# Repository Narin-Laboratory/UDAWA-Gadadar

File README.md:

# UDAWA Gadadar - Universal Digital Agriculture Workflow Assistant

Welcome to the official firmware repository for UDAWA Gadadar, a key component of the UDAWA Smart System! This project is dedicated to empowering small-scale farmers with precision agriculture technology, making farming more efficient, sustainable, and fun.

## What is UDAWA?

UDAWA, which stands for **Universal Digital Agriculture Workflow Assistant**, is an open-source platform designed to bring the power of the Internet of Things (IoT) to agriculture. Our mission is to create a "peasant-centric" ecosystem of hardware and software tools that are affordable, easy to use, and adaptable to the needs of small farmers.

We believe that technology can help bridge the gap between traditional farming practices and modern, data-driven agriculture. By providing tools for monitoring, control, and automation, UDAWA helps farmers save time, reduce waste, and gain valuable insights into their operations.

## UDAWA Gadadar: The Smart Power Controller

UDAWA Gadadar is the muscle of the UDAWA ecosystem. It's a smart power controller that allows you to manage and automate various electrical appliances in your greenhouse or farm, such as:

- Pumps for irrigation and fertigation
- Fans and blowers for climate control
- Grow lights for supplemental lighting
- Misters and foggers for humidity control

### Key Features:

- **Remote Control:** Turn your farm equipment on and off from anywhere using your smartphone.
- **Automation:** Schedule tasks based on time, duration, or sensor data (e.g., turn on the fan when the temperature rises).
- **Energy Monitoring:** Keep track of your electricity consumption to optimize usage and reduce costs.
- **Modular Design:** UDAWA Gadadar comes with four independent channels, each with its own energy sensor.
- **Open Source:** The firmware is fully open-source, allowing you to customize and extend its functionality.

## Hardware

The UDAWA Gadadar hardware is designed to be robust, reliable, and easy to assemble. Here's a sneak peek at the device:

**Image Placeholder: UDAWA Gadadar Device**
``

## Software

The UDAWA Gadadar firmware is built on the PlatformIO ecosystem and runs on the popular ESP32 microcontroller. It's packed with features to ensure seamless integration with the UDAWA cloud platform and mobile app.

**Image Placeholder: UDAWA Mobile App Screenshot**
``

## Getting Started

Ready to build your own UDAWA Gadadar? Here's how to get started:

1. **Set up your environment:**
   ```bash
   ./setup_env.sh
   ```
2. **Build the firmware:**
   ```bash
   pio run -e Gadadar4Ch
   ```
3. **Upload the firmware to your ESP32.**
4. **Provision your device using the UDAWA mobile app.**

For more detailed instructions, please refer to our documentation (coming soon!).

## Contributing

UDAWA is a community-driven project, and we welcome contributions from everyone! Whether you're a farmer, an engineer, a developer, or a hobbyist, there are many ways you can get involved:

- **Report bugs and suggest features** by opening an issue.
- **Submit pull requests** with your own code, documentation, or design improvements.
- **Share your UDAWA projects** with the community.

## Our Dearest Contributors

This project would not be possible without the amazing contributions of the following individuals:

- I Wayan Aditya Suranata
- I Nyoman Kusuma Wardana
- Ngakan Kutha Krisnawijaya
- Gede Humaswara Prathama
- Dhimas Prayoga
- I Made Surya Adi Putra
- I Gusti Ngurah Darma Paramartha
- Adie Wahyudi Oktavia Gama
- I Putu Widia Prasetya
- I Nyoman Hary Kurniawan
- I Made Pande Darma Yuda
- I Kadek Arta Wiguna
- I Gusti Gede Dhipa Andaresta
- Hendri Gunawan
- Andhika Bintar Lorenzo Kristian Reinnamah
- I Gusti Nathan Agung Tanaka
- Muhammad Zafran Zulkifli
- You

## License

UDAWA Gadadar is licensed under the **GNU Affero General Public License v3.0**. This means you are free to use, modify, and distribute the software, but you must also make your modifications available under the same license. For more details, see the [LICENSE](LICENSE) file.

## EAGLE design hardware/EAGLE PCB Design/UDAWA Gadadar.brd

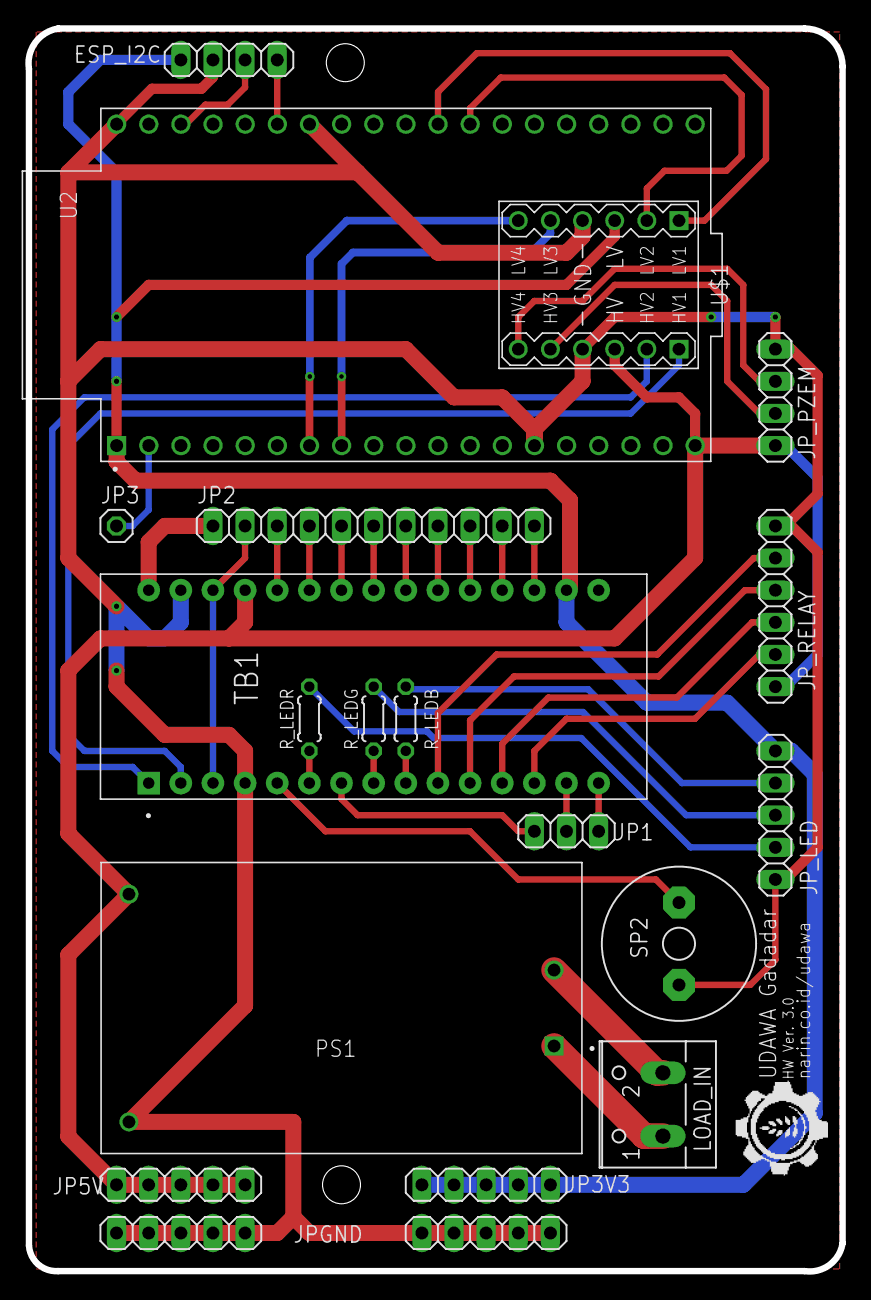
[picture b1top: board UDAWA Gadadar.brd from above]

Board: 2 copper layers, 64.3 x 98.2 mm, 20 parts (0 on the bottom side), 41 nets.

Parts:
ESP_I2C: 1X04
JP1: 1X03
JP2: 1X11
JP3: PINHD-1X1; 1X01
JP3V3, JP5V: 1X05
JPGND, JPGND1: 1X05
JP_LED: 1X05
JP_PZEM: 1X04
JP_RELAY: 1X06
LOAD_IN: W237-102
PS1: HLK-5M05; CONV_HLK-5M05
R_LEDB: 1K; 0204/5
R_LEDG: 1K; 0204/5
R_LEDR: 1K; 0204/5
SP2: AL60P
TB1: ARDUINO_NANO; SHIELD_ARDUINO_NANO
U2: ESP32-DEVKITC-32U; MODULE_ESP32-DEVKITC-32U
U$1: LEVEL-SHIFTER-4CH

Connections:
3V3: ESP_I2C.1, JP3V3.1, JP3V3.2, JP3V3.3, JP3V3.4, JP3V3.5, JP_LED.5, TB1.17, U2.1, U$1.J1.3
5V: JP5V.1, JP5V.2, JP5V.3, JP5V.4, JP5V.5, JP_PZEM.4, JP_RELAY.6, PS1.4, TB1.27, U2.19, U$1.J2.3
AC1: LOAD_IN.1, PS1.1
AC2: LOAD_IN.2, PS1.2
CA0: JP2.10, TB1.19
CA1: JP2.9, TB1.20
CA2: JP2.8, TB1.21
CA3: JP2.7, TB1.22
CA6: JP2.4, TB1.25
CA7: JP2.3, TB1.26
CAREF: JP2.11, TB1.18
CD4: JP1.1, TB1.7
CD11: JP1.2, TB1.14
CD12: JP1.3, TB1.15
CH1: JP_RELAY.2, TB1.10
CH2: JP_RELAY.3, TB1.11
CH3: JP_RELAY.4, TB1.12
CH4: JP_RELAY.5, TB1.13
COMCU_RX: TB1.2, U$1.J2.1
COMCU_SCL: JP2.5, TB1.24
COMCU_SDA: JP2.6, TB1.23
COMCU_TX: TB1.1, U$1.J2.2
CRST: JP2.2, TB1.3, TB1.28
CVIN: JP2.1, TB1.30
ESP_SCL: ESP_I2C.3, U2.36
ESP_SDA: ESP_I2C.4, U2.33
GND: ESP_I2C.2, JPGND.1, JPGND.2, JPGND.3, JPGND.4, JPGND.5, JPGND1.1, JPGND1.2, JPGND1.3, JPGND1.4, JPGND1.5, JP_LED.1, JP_PZEM.1, JP_RELAY.1, PS1.3, SP2.1, TB1.4, TB1.29, U2.14, U2.32, U2.38, U$1.J1.4, U$1.J2.4
MEN: JP3.1, U2.2
PIN_BUZZER: SP2.2, TB1.5
PIN_LEDB: R_LEDB.1, TB1.9
PIN_LEDG: R_LEDG.1, TB1.8
PIN_LEDR: R_LEDR.1, TB1.6
PZEM_RX: JP_PZEM.3, U$1.J2.5
PZEM_TX: JP_PZEM.2, U$1.J2.6
RLEDB: JP_LED.4, R_LEDB.2
RLEDG: JP_LED.3, R_LEDG.2
RLEDR: JP_LED.2, R_LEDR.2
S1_RX: U2.7, U$1.J1.6
S1_TX: U2.8, U$1.J1.5
S2_RX: U2.27, U$1.J1.2
S2_TX: U2.28, U$1.J1.1

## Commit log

2023-01-01 [UNTESTED] PZEM 004 implemented
2023-01-02 WIP Power & Environemtn Sensor
2023-01-06 [WIP] bme280 weather sensor
2023-01-06 [WIP] bme280
2023-01-09 [WIP] sensors
2023-01-11 BME280 Checkpoint
2023-01-11 checkpoint relay, wip PZEM
2023-01-14 GPIO2 Not Working for Serial1, moved temporary to CoMCU D11 & D12
2023-01-17 PZEM Pin Patch from 2 to 32
2023-01-28 Telemetry bug fix
2023-01-29 led bug fix
2023-01-30 alarm
2023-02-05 v0.0.3
2023-02-21 Board & Schematic
2023-02-23 Updated LICENSE
2023-02-23 Updated header
2023-03-06 logo
2023-03-06 Interface init
2023-03-09 Updated PCB FIles
2023-03-09 added screenshot
2023-03-09 Added device photo
2023-03-09 Rename
2023-03-12 interface refactore
2023-03-13 iface wip
2023-03-16 New DOI
2023-04-13 Bugfix on 0 active relay
2023-04-13 removed .ini
2023-04-13 wip alarm
2023-04-14 BETA Test Alarm
2023-04-14 selfDiagnostic
2023-04-14 startup alarm
2023-04-14 self diagnosis
2023-04-16 First working prototype for relayControlByMultiTime
2023-04-16 updated sensor data aggregation, ver.0.0.2
2023-04-16 0.0.3 Bug FIxes, Features Improvement
2023-04-17 WIP IoT bugfix + cloud toggle
2023-04-17 iface update
2023-04-17 iface bug fix
2023-04-17 remove console.log
2023-04-17 iface autoreload
2023-04-18 bug fix on power telemetry
2023-04-18 v0.0.4
2023-04-18 ws telemetry
2023-04-18 dtCyMT to rlyActMT
2023-04-18 v0.0.5 added SPIFFS HTTP OTA
2023-04-18 added v0.0.5 lib to platformio.ini
2023-04-18 bug fix: _watt.Add
2023-04-18 sensor telemetry
2023-04-18 [WIP] PZEM Bug Serial Broken
2023-04-18 Promising KWH soution
2023-04-19 checkpoint
2023-04-20 WIP - Task based
2023-04-20 Code refactore - Backward Incompatible
2023-04-20 added Taskscheduler
2023-04-25 Total refactor
2023-04-25 removed log
2023-04-29 untested
2023-04-29 unstested
2023-05-09 AsyncTCP/Webserver Conflict with ArduinoOTA
2023-05-21 design
2023-06-11 Added autoOff for manual switch
2023-10-30 v0.0.11
2023-10-30 fixed tbota
2023-11-10 ini update
2023-11-19 update gitignore
2023-11-19 testing new stacksize. v.0.0.12
2023-11-23 dynamic pin for pzem
2023-11-23 fix typo
2023-12-06 otatools
2023-12-09 ener
2023-12-18 0.0.15 added alarm threshold
2024-03-06 updated lib
2025-10-08 Neo porting
2025-10-08 updated gitignore
2025-10-08 feat: Refactor and enhance power sensor task
    This commit significantly improves the `coreroutinePowerSensorTaskRoutine` by introducing several new features and enhancements.
    - Implements an averaging algorithm to provide more realistic telemetry data over time, while still sending instantaneous readings for real-time attributes and WebSocket updates.
    - Adds a dummy data generation mode, controlled by the `fPowerSensorDummy` flag in `appConfig`, to allow for testing without a physical sensor.
    - Makes the alarm processing interval configurable via the `powerSensorAlarmTimer` setting in `appConfig`, replacing the previous hardcoded value.
    - Reduces verbose logging for sensor reading failures t
2025-10-09 refactor: Enhance power sensor data collection and dummy mode
    This commit addresses feedback from the pull request review, further improving the `coreroutinePowerSensorTaskRoutine`.
    - **Advanced Data Collection:** The telemetry logic is enhanced to track and send more meaningful metrics, including the minimum, maximum, and average voltage, as well as the total energy consumed (i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
    - **State-Aware Dummy Data:** The dummy data generator is now much smarter. It calculates the expected power load by summing the wattage of all active relays, and simulates a small standby power draw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
2025-10-09 fixup: Refine power sensor logic and expand telemetry
    This commit incorporates the final round of feedback from the pull request review.
    - The dummy data generator's standby power simulation is now adjusted to a more realistic 5-6 watts.
    - The telemetry data aggregation is expanded to include minimum, maximum, and average values for all sensor metrics (amperage, power factor, and frequency), providing a more comprehensive dataset.
2025-10-09 Improve logging, activate the dummy power data generator
2025-10-09 Create build-test.yml for PlatformIO workflow
2025-10-09 Specify working directory for PlatformIO build
    Updated the build-test workflow to specify the working directory for the PlatformIO build command.
2025-10-09 Add file listing step to build workflow
    Added a step to list all files in the repository before building the PlatformIO project.
2025-10-09 Fix workflow to run environment setup script
2025-10-09 PlatformIO Build Test
2025-10-09 Add build test badge to README
2025-10-09 updated model name
2025-10-09 updated UI
2025-10-09 feat: Add FSUpdate RPC and centralized storage saving
    This commit introduces two main enhancements:
    1. **New "FSUpdate" RPC:** A new remote procedure call (RPC) named "FSUpdate" has been added. When invoked, this RPC triggers the filesystem download process. A corresponding `fFSUpdateRPCSubscribed`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
    2. **Centralized Storage Saving:** A new function, `coreroutineSaveAllStorage`, has been created to consolidate the logic for saving all critical storage objects (`config`, `appConfig`, `appState`, `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
    The "FSUpdate" RPC c
2025-10-09 refactor: Improve FSUpdate RPC and storage saving logic
    This commit refactors the "FSUpdate" RPC implementation to improve robustness and clarity.
    The key changes are:
    - The "FSUpdate" RPC now creates a dedicated FreeRTOS task to handle the filesystem download asynchronously. This prevents the main loop from being blocked by a long-running operation.
    - The `fFSDownloading` flag has been removed from the `CrashState` struct as it is no longer needed.
    - The logic for saving all storage objects is now correctly placed within the `coreroutineFSDownloader` function, ensuring data is persisted before the download starts.
    - A clarifying comment has been added to explain the saving mechanism for th
2025-10-09 refactor: Add WebSocket progress broadcasting and consistent saving
    This commit introduces two main improvements to the filesystem update process:
    1. **WebSocket Progress Broadcasting:** The `coreroutineFSDownloader` function now sends real-time progress updates to the UI via WebSockets. It broadcasts structured JSON messages for the start, pro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
    2. **Consistent Configuration Saving:** All `config.save()` calls within `coreroutineFSDownloader` have been replaced with the centralized `coreroutineSaveAllStorage()` function. This ensures that al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
2025-10-09 Cleaning debug
2025-10-09 updated cfg
2025-10-09 updated bin URL
2025-10-09 http improve
2025-10-10 add ipad key
2025-10-10 added attr
2025-10-10 add batt attr
2025-10-11 Added new RPC
2025-10-11 added stateSave
2025-10-14 FIxed typo
2025-10-14 docs: Create a fun and informative project README
    This commit replaces the basic README.md with a comprehensive and engaging version that better introduces the UDAWA Gadadar project.
    The new README includes:
    - A detailed explanation of the UDAWA platform and its goals.
    - A list of key features for the Gadadar device.
    - Placeholders for hardware and software images.
    - A "Getting Started" guide for new users.
2025-11-05 bug fix
2025-11-05 added power check
2025-11-07 Last minute patch
2025-11-09 feat(wifi): connect to strongest access point
    Introduces a new mechanism to scan for available WiFi networks and connect to the access point with the strongest signal (highest RSSI) that matches the configured SSID.
    This enhancement improves connection stability in environments with multiple access points for the same network, preventing the device from connecting to a weaker or more distant AP.
    The `UdawaWiFiHelper` class now includes a `connectToStrongestAP` method that:
    - Scans for all available networks.
    - Identifies the AP with the strongest signal for the configured SSID.
    - Connects to the selected AP using its BSSID.
2025-11-09 improve wifi, secure logging, improve failsafe
2025-11-09 switch to neo from legacy

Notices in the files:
parts and their libraries:
diy-modules: Released under the Creative Commons Attribution 4.0 International License: http://creativecommons.org/licenses/by/4.0
